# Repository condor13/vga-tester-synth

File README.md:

# vga-tester-synth
vga tester
It has not been testet. 
Will add BOM PANEL cutout and GRBRS for fab.

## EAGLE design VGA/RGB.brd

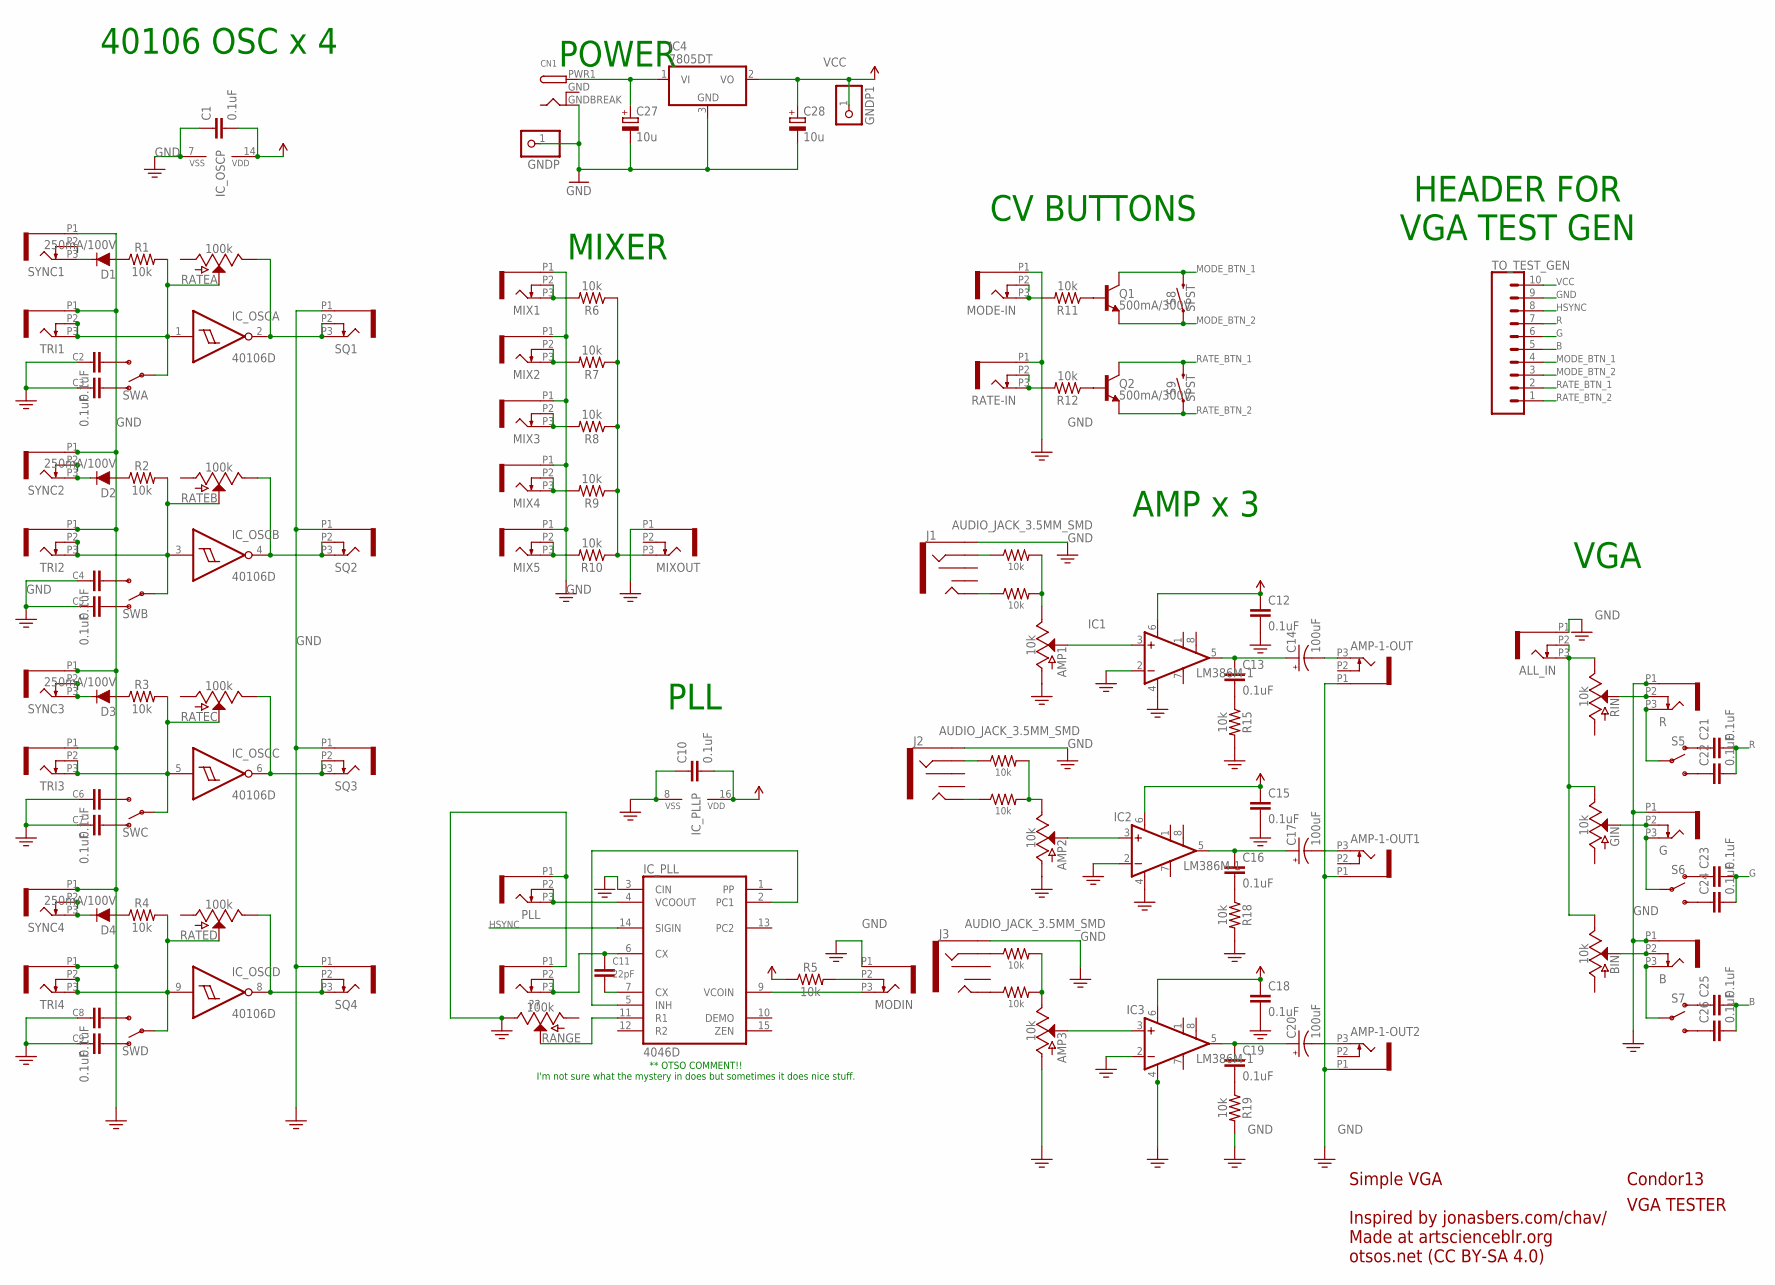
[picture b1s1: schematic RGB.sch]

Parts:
??: PJ301_THONKICONN6; WQP_PJ_301M6
ALL_IN: PJ301_THONKICONN6; WQP_PJ_301M6
AMP1, AMP2, AMP3: 10k; POT-PTH-ALPS-KIT
AMP-1-OUT, AMP-1-OUT1, AMP-1-OUT2: PJ301_THONKICONN6; WQP_PJ_301M6
B: PJ301_THONKICONN6; WQP_PJ_301M6
BIN: 10k; POT-PTH-ALPS-KIT
C1, C2, C3, C4, C5, C6, C7, C8, C9, C10, C12, C13, C15, C16, C18, C19, C21, C22, C23, C24, C25, C26: 0.1uF; 0603
C11: 22pF; 0603
C14, C17, C20: 100uF; PANASONIC_D
C27, C28: 10u; PANASONIC_D
CN1: DCBARRELSMT; DCJACK_2MM_SMT
D1, D2, D3, D4: 250mA/100V; SOD-323
G: PJ301_THONKICONN6; WQP_PJ_301M6
GIN: 10k; POT-PTH-ALPS-KIT
GNDP, GNDP1: PINHD-1X1CB; 1X01-CLEANBIG
IC1, IC2, IC3: LM386M-1; SO08
IC4: 7805DT; TO252
IC_OSC: 40106D; SO14
IC_PLL: 4046D; SO16
J1, J2, J3: AUDIO_JACK_3.5MM_SMD; AUDIO-JACK-3.5MM-SMD
MIX1, MIX2, MIX3, MIX4, MIX5: PJ301_THONKICONN6; WQP_PJ_301M6
MIXOUT: PJ301_THONKICONN6; WQP_PJ_301M6
MODE-IN: PJ301_THONKICONN6; WQP_PJ_301M6
MODIN: PJ301_THONKICONN6; WQP_PJ_301M6
PLL: PJ301_THONKICONN6; WQP_PJ_301M6
Q1, Q2: 500mA/300V; SOT23-3
R: PJ301_THONKICONN6; WQP_PJ_301M6
R1, R2, R3, R4, R5, R6, R7, R8, R9, R10, R11, R12, R13, R14, R15, R16, R17, R18, R19, R20, R21: 10k; 0603
RANGE: 100k; POT-PTH-ALPS-KIT
RATE-IN: PJ301_THONKICONN6; WQP_PJ_301M6
RATEA: 100k; POT-PTH-ALPS-KIT
RATEB: 100k; POT-PTH-ALPS-KIT
RATEC: 100k; POT-PTH-ALPS-KIT
RATED: 100k; POT-PTH-ALPS-KIT
RIN: 10k; POT-PTH-ALPS-KIT
S5, S6, S7: SWITCH-SPDT-PTH-11.6X4.0MM-LOCK; SWITCH_SPDT_PTH_11.6X4.0MM_LOCK
S8, S9: SPST; TACTILE_SWITCH_SMD_6.2MM_TALL
SQ1, SQ2, SQ3, SQ4: PJ301_THONKICONN6; WQP_PJ_301M6
SWA: SWITCH-SPDT-PTH-11.6X4.0MM-LOCK; SWITCH_SPDT_PTH_11.6X4.0MM_LOCK
SWB: SWITCH-SPDT-PTH-11.6X4.0MM-LOCK; SWITCH_SPDT_PTH_11.6X4.0MM_LOCK
SWC: SWITCH-SPDT-PTH-11.6X4.0MM-LOCK; SWITCH_SPDT_PTH_11.6X4.0MM_LOCK
SWD: SWITCH-SPDT-PTH-11.6X4.0MM-LOCK; SWITCH_SPDT_PTH_11.6X4.0MM_LOCK
SYNC1, SYNC2, SYNC3, SYNC4: PJ301_THONKICONN6; WQP_PJ_301M6
TO_TEST_GEN: CONN_102MMSMD; 1X10-2MM-SMD
TRI1, TRI2, TRI3, TRI4: PJ301_THONKICONN6; WQP_PJ_301M6

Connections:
3.3V: IC2.4 (GND)
B: C25.2, C26.2, TO_TEST_GEN.5
G: C23.2, C24.2, TO_TEST_GEN.6
GND: ??.P1 (1), ALL_IN.P1 (1), AMP1.P$3 (A), AMP2.P$3 (A), AMP3.P$3 (A), AMP-1-OUT.P1 (1), AMP-1-OUT1.P1 (1), AMP-1-OUT2.P1 (1), B.P1 (1), C1.1, C2.2, C3.2, C4.2, C5.2, C6.2, C7.2, C8.2, C9.2, C10.1, C12.2, C15.2, C18.2, C27.-, C28.-, CN1.GNDBREAK (GND), G.P1 (1), GNDP.1, IC1.2 (-IN), IC1.4 (GND), IC2.2 (-IN), IC3.2 (-IN), IC3.4 (GND), IC4.3 (GND), IC_OSC.7 (VSS), IC_PLL.3 (CIN), IC_PLL.8 (VSS), J1.SLEEVE, J2.SLEEVE, J3.SLEEVE, MIX1.P1 (1), MIX2.P1 (1), MIX3.P1 (1), MIX4.P1 (1), MIX5.P1 (1), MIXOUT.P1 (1), MODE-IN.P1 (1), MODIN.P1 (1), PLL.P1 (1), R.P1 (1), R15.2, R18.2, R19.2, RANGE.P$1 (E), RATE-IN.P1 (1), SQ1.P1 (1), SQ2.P1 (1), SQ3.P1 (1), SQ4.P1 (1), SYNC1.P1 (1), SYNC2.P1 (1), SYNC3.P1 (1), SYNC4.P1 (1), TO_TEST_GEN.9, TRI1.P1 (1), TRI2.P1 (1), TRI3.P1 (1), TRI4.P1 (1)
GNDBREAK: CN1.GND (GNDBREAK)
HSYNC: IC_PLL.14 (SIGIN), TO_TEST_GEN.8
MODE_BTN_1: Q1.3 (C), S8.B2 (2), TO_TEST_GEN.4
MODE_BTN_2: Q1.2 (E), S8.A2 (1), TO_TEST_GEN.3
unnamed: IC_PLL.2 (PC1), IC_PLL.5 (INH)
unnamed: ??.P2 (2), ??.P3 (3), C11.1, IC_PLL.6 (CX)
unnamed: C11.2, IC_PLL.7 (CX)
unnamed: MIX1.P2 (2), MIX1.P3 (3), R6.2
unnamed: MIX2.P2 (2), MIX2.P3 (3), R7.2
unnamed: MIX3.P2 (2), MIX3.P3 (3), R8.2
unnamed: MIX4.P2 (2), MIX4.P3 (3), R9.2
unnamed: AMP1.P$2 (S), IC1.3 (+IN)
unnamed: C13.2, R15.1
unnamed: MIX5.P2 (2), MIX5.P3 (3), R10.2
unnamed: MIXOUT.P3 (3), R6.1, R7.1, R8.1, R9.1, R10.1
unnamed: C13.1, C14.+, IC1.5 (OUT)
unnamed: ALL_IN.P3 (3), BIN.P$1 (E), GIN.P$1 (E), RIN.P$1 (E)
unnamed: D2.A, R2.1
unnamed: R.P2 (2), RIN.P$2 (S)
unnamed: R.P3 (3), S5.2
unnamed: IC_OSC.2 (O), RATEA.P$1 (E), SQ1.P2 (2), SQ1.P3 (3)
unnamed: D2.C, SYNC2.P3 (3)
unnamed: IC_OSC.4 (O), RATEB.P$1 (E), SQ2.P2 (2), SQ2.P3 (3)
unnamed: C4.1, SWB.3 (S)
unnamed: C22.1, S5.3 (S)
unnamed: C21.1, S5.1 (O)
unnamed: G.P2 (2), GIN.P$2 (S)
unnamed: G.P3 (3), S6.2
unnamed: C24.1, S6.3 (S)
unnamed: C23.1, S6.1 (O)
unnamed: AMP1.P$1 (E), R13.2, R14.2
unnamed: D1.C, SYNC1.P3 (3)
unnamed: D1.A, R1.1
unnamed: IC_OSC.1 (I), R1.2, RATEA.P$2 (S), SWA.2, TRI1.P2 (2), TRI1.P3 (3)
unnamed: C2.1, SWA.3 (S)
unnamed: C3.1, SWA.1 (O)
unnamed: C5.1, SWB.1 (O)
unnamed: D3.A, R3.1
unnamed: D3.C, SYNC3.P3 (3)
unnamed: IC_OSC.6 (O), RATEC.P$1 (E), SQ3.P2 (2), SQ3.P3 (3)
unnamed: IC_OSC.5 (I), R3.2, RATEC.P$2 (S), SWC.2, TRI3.P2 (2), TRI3.P3 (3)
unnamed: C6.1, SWC.3 (S)
unnamed: C7.1, SWC.1 (O)
unnamed: D4.A, R4.1
unnamed: D4.C, SYNC4.P3 (3)
unnamed: IC_OSC.8 (O), RATED.P$1 (E), SQ4.P2 (2), SQ4.P3 (3)
unnamed: IC_OSC.9 (I), R4.2, RATED.P$2 (S), SWD.2, TRI4.P2 (2), TRI4.P3 (3)
unnamed: C8.1, SWD.3 (S)
unnamed: C9.1, SWD.1 (O)
unnamed: IC_PLL.11 (R1), RANGE.P$2 (S)
unnamed: MODIN.P2 (2), R5.2
unnamed: IC_PLL.9 (VCOIN), MODIN.P3 (3)
unnamed: J1.RING, R13.1
unnamed: J1.TIP, R14.1
unnamed: AMP-1-OUT.P3 (3), C14.-
unnamed: AMP2.P$2 (S), IC2.3 (+IN)
unnamed: C16.2, R18.1
unnamed: C16.1, C17.+, IC2.5 (OUT)
unnamed: J2.RING, R16.1
unnamed: J2.TIP, R17.1
unnamed: AMP2.P$1 (E), R16.2, R17.2
unnamed: AMP-1-OUT1.P3 (3), C17.-
unnamed: AMP3.P$2 (S), IC3.3 (+IN)
unnamed: C19.2, R19.1
unnamed: C19.1, C20.+, IC3.5 (OUT)
unnamed: B.P2 (2), BIN.P$2 (S)
unnamed: B.P3 (3), S7.2
unnamed: J3.RING, R20.1
unnamed: AMP-1-OUT2.P3 (3), C20.-
unnamed: C26.1, S7.3 (S)
unnamed: C25.1, S7.1 (O)
unnamed: Q1.1 (B), R11.1
unnamed: MODE-IN.P3 (3), R11.2
unnamed: Q2.1 (B), R12.1
unnamed: R12.2, RATE-IN.P3 (3)
unnamed: AMP3.P$1 (E), R20.2, R21.2
unnamed: J3.TIP, R21.1
unnamed: IC_OSC.3 (I), R2.2, RATEB.P$2 (S), SWB.2, TRI2.P2 (2), TRI2.P3 (3)
unnamed: C27.+, CN1.PWR1 (PWR), IC4.1 (VI)
unnamed: IC_PLL.4 (VCOOUT), PLL.P2 (2), PLL.P3 (3)
R: C21.2, C22.2, TO_TEST_GEN.7
RATE_BTN_1: Q2.3 (C), S9.B2 (2), TO_TEST_GEN.2
RATE_BTN_2: Q2.2 (E), S9.A2 (1), TO_TEST_GEN.1
VCC: C1.2, C10.2, C12.1, C15.1, C18.1, C28.+, GNDP1.1, IC1.6 (VS), IC2.6 (VS), IC3.6 (VS), IC4.2 (VO), IC_OSC.14 (VDD), IC_PLL.16 (VDD), R5.1, TO_TEST_GEN.10

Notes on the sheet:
** OTSO COMMENT!! I'm not sure what the mystery in does but sometimes it does nice stuff.
Condor13
Simple VGA Inspired by jonasbers.com/chav/ Made at artscienceblr.org otsos.net (CC BY-SA 4.0)
40106 OSC x 4
MIXER
PLL
CV BUTTONS
AMP x 3
VGA
HEADER FOR VGA TEST GEN
POWER
VGA TESTER

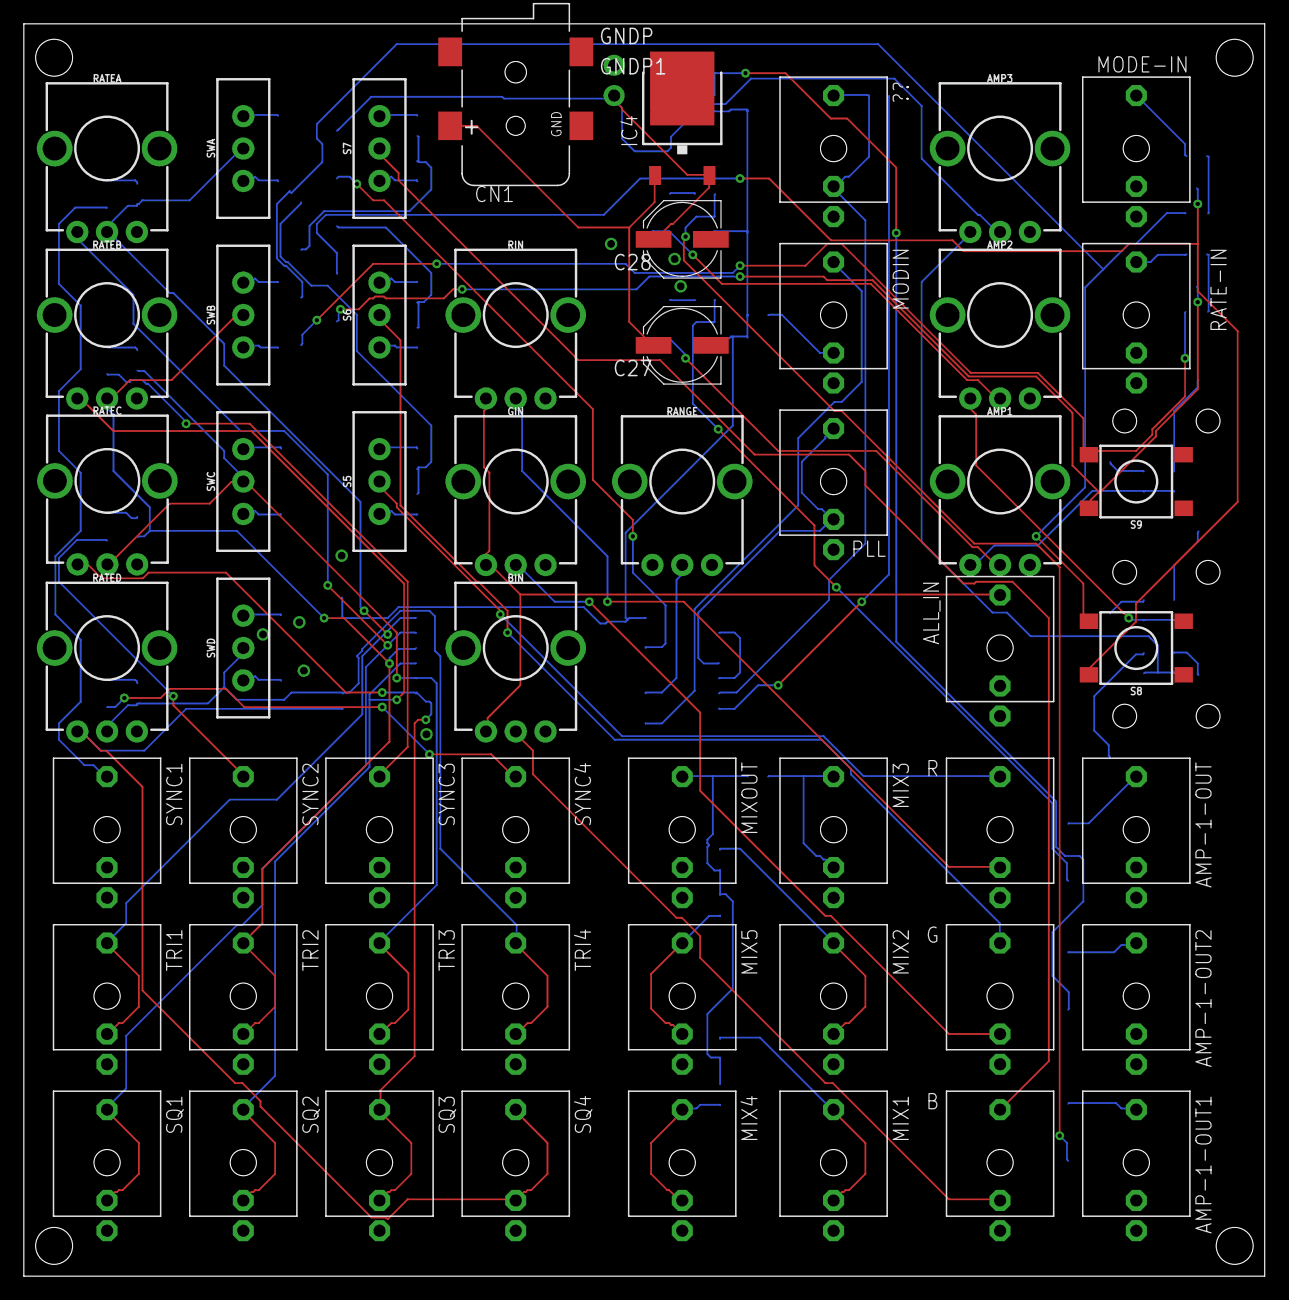
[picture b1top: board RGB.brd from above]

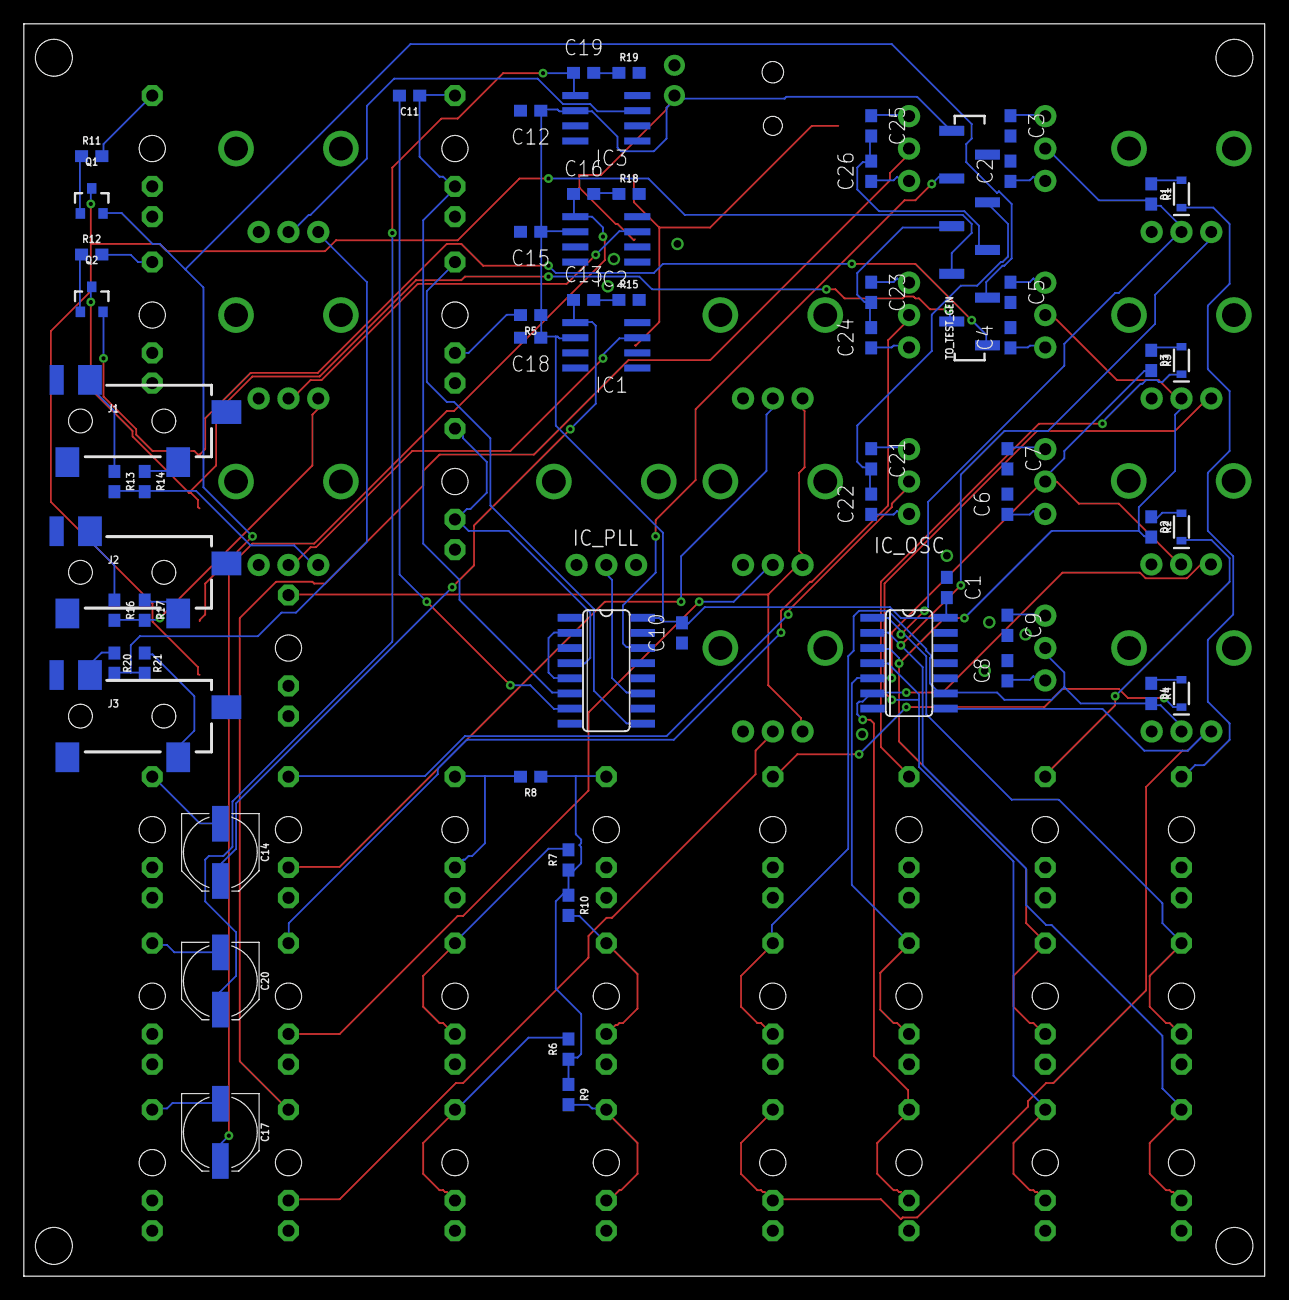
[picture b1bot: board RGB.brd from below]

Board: 2 copper layers, 104.1 x 105.1 mm, 118 parts (62 on the bottom side), 86 nets.

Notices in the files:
parts and their libraries:
SparkFun-Connectors: Licensing: Creative Commons ShareAlike 4.0 International - https://creativecommons.org/licenses/by-sa/4.0
